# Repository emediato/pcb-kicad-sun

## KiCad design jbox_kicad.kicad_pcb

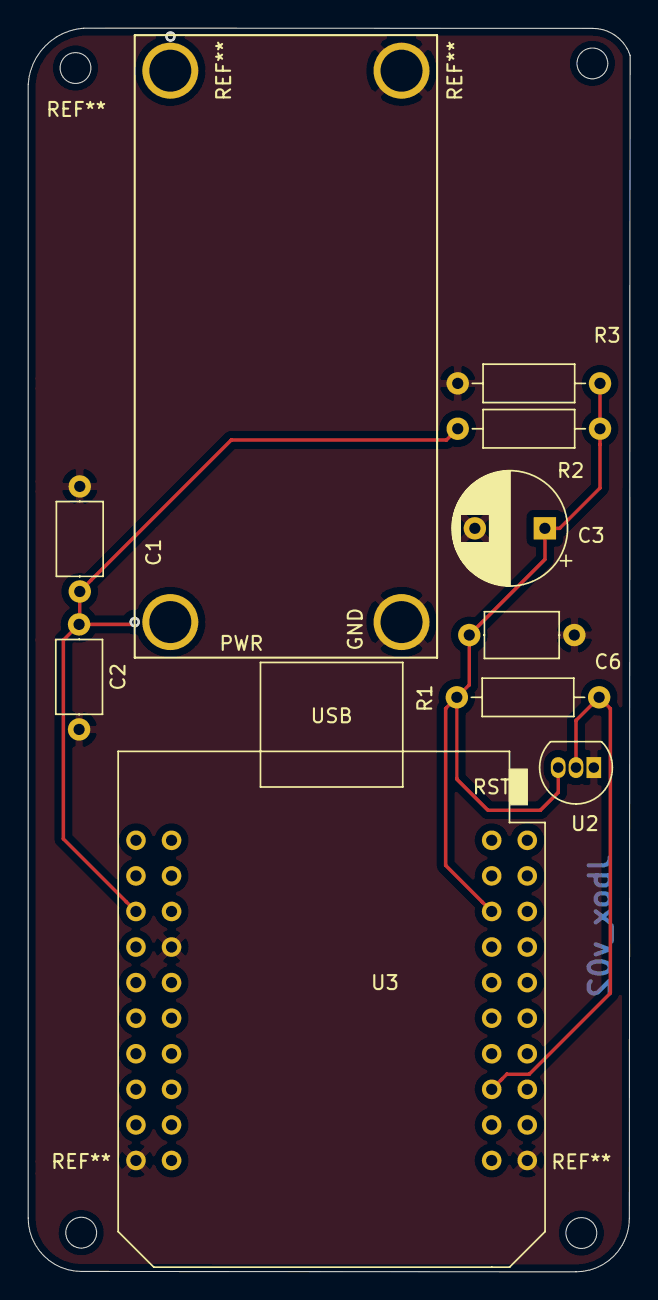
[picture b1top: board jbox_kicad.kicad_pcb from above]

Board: 2 copper layers, 43.0 x 88.8 mm, 11 parts (0 on the bottom side), 4 nets.

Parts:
C1: 100uF; C_Axial_L5.1mm_D3.1mm_P7.50mm_Horizontal
C2: 10uF; C_Axial_L5.1mm_D3.1mm_P7.50mm_Horizontal
C3: 22uF; CP_Radial_D8.0mm_P5.00mm
C6: 0.1uF; C_Axial_L5.1mm_D3.1mm_P7.50mm_Horizontal
GND: SolderWirePad_1x01_Drill1.5mm
PWR: SolderWirePad_1x01_Drill1.5mm
R1: 4.7k; R_Axial_DIN0207_L6.3mm_D2.5mm_P10.16mm_Horizontal
R2: 1000; R_Axial_DIN0207_L6.3mm_D2.5mm_P10.16mm_Horizontal
R3: 2000; R_Axial_DIN0207_L6.3mm_D2.5mm_P10.16mm_Horizontal
U2: DS18B20; TO-92_Inline
U3: mini_esp32; ESP32_mini

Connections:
DQA0: R1.1, U2.2, U3.6
GND: C1.2, C2.2, C3.2, C6.2, GND.1, R3.2, U2.1, U3.1, U3.22, U3.33
VDD5: C1.1, C2.1, R2.1, U3.36
VDD33: C3.1, C6.1, R1.2, R2.2, R3.1, U2.3, U3.16

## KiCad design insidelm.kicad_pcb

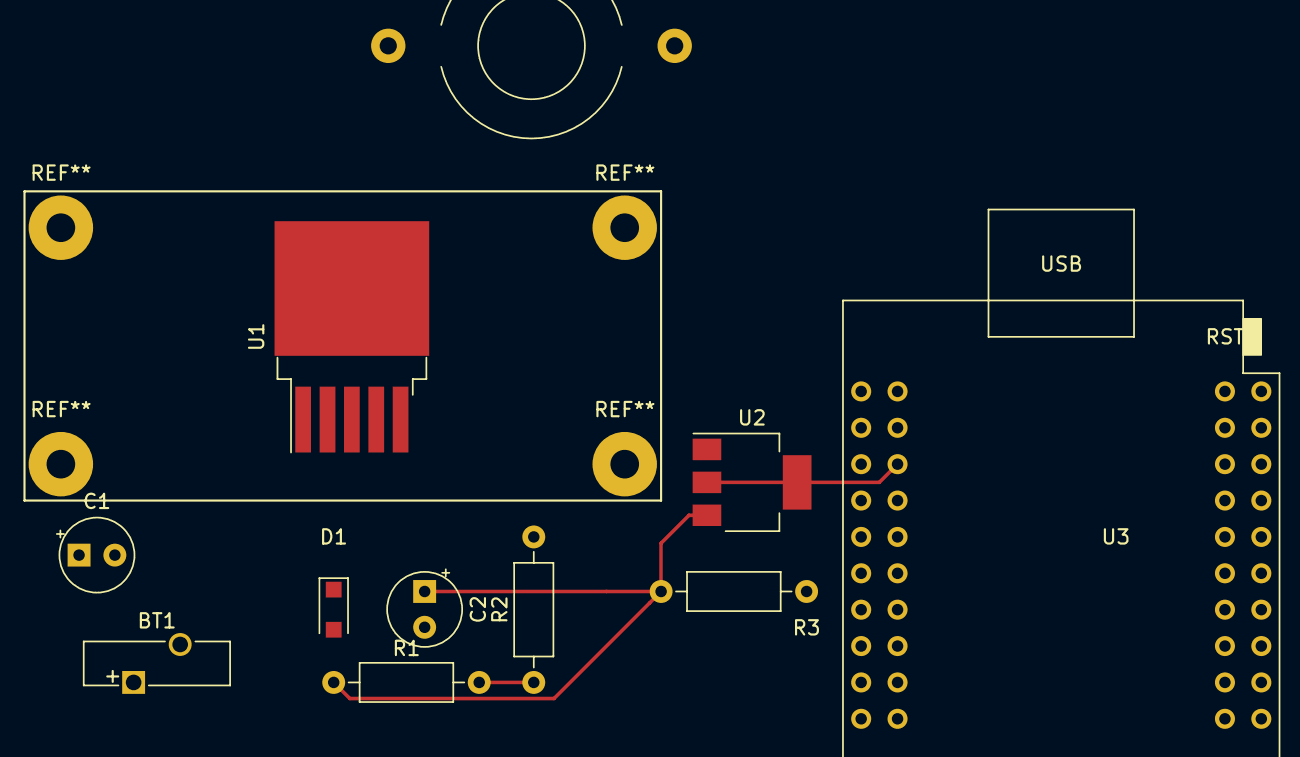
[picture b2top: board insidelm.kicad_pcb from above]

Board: 2 copper layers, 11 parts (0 on the bottom side), 6 nets.

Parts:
BT1: 40.8V; Battery_Panasonic_CR1025-VSK_Vertical_CircularHoles
C1: 470u; CP_Radial_Tantal_D5.0mm_P2.50mm
C2: 330u; CP_Radial_Tantal_D5.0mm_P2.50mm
D1: MBRS360; D_SOD-123F
L1: 47u; L_Toroid_Horizontal_D12.7mm_P20.00mm_Diameter14-5mm_Amidon-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
R1: 6.12k; R_Axial_DIN0207_L6.3mm_D2.5mm_P10.16mm_Horizontal
R2: 2k; R_Axial_DIN0207_L6.3mm_D2.5mm_P10.16mm_Horizontal
R3: 1.6k; R_Axial_DIN0207_L6.3mm_D2.5mm_P10.16mm_Horizontal
U1: LM2596HVS; TO-263-5_TabPin3
U2: AMS1117-5.0; SOT-223-3_TabPin2
U3: mini_esp32; ESP32_mini

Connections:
GND: BT1.2, C1.2, C2.2, D1.2, R2.2, R3.2, U1.3, U1.4, U2.1, U3.1, U3.22, U3.33
unnamed: BT1.1, C1.1, U1.1
unnamed: C2.1, L1.2, R1.1, R3.1, U2.3
unnamed: D1.1, L1.1, U1.2
unnamed: R1.2, R2.1, U1.5
unnamed: U2.2, U3.35

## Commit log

2021-05-10 2nd version
